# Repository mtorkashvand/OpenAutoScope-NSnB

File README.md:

# OpenAutoScope-NSnB
OpenAutoScope is a bright-field tracking microscope capable of delivering light stimulus to freely behaing c. elegans. This system is designed and assembled by Nate Cermak 
and the ripository containing information on how to assemble the system is found here:  
[OpenAutoScope by Nate Cermak](https://bitbucket.org/natecermak/openautoscope/src/master/)  
For convenience I have copied the content of the mentioned repository here.  

OpenAutoScope-NSnB repository is an open-source software developed during the NSnB 2022 program to pilot the system.

## Installation

1- Clone this repository:  
```
git clone https://github.com/mtorkashvand/OpenAutoScope-NSnB.git
```  
2- Navigate into the clone repo and use the `.yml` file to create a conda environment named `wormtracker`:  
```
cd OpenAutoScope-NSnB  
conda env create -f environment.yml  
```  
3- Activate `wormtracker` environment and install the software inside it:  
```  
activate wormtracker  
python setup.py develop  
```  
4- Open a File Explorer window and navigate to `OpenAutoScope-NSnB -> wormtracker_scope -> bin -> debug`, then click on the address bar and copy the absolute path to this folder.  

5- In the Windows search bar type `edit the system environment variables` and open it.  

6- Click on `Environment Variables ...`  

7- In the opened window, under `System Varibales` click on `New ...`  

8- Set the variable name to `WORMTRACKER_BIN` and set the variable value to the absolute path copied in step 4, and click on `OK`  

9- Next, look for the `Path` variable under the `System Variables`, double-click to open it, click on `New` and add `%WORMTRACKER_BIN%` and click on `OK`  

The Installation is completed  

## Running the System

1. Open a command prompt, and activate `wormtracker` environment  
```
activate wormtracker
```
2. Run the system using the following command:
```
wormtracker --directory=<data output path> --exposure=<exposure time in microseconds>
```  
exapmle: if you want your data to be saved in a folder named `data` in the C drive, and the exposure time is 1500us, then the command to run the system is:  
```
wormtracker --directory=C:\data --exposure=1500
```  
Note: A default value for the exposure time and the data directory could be set in `wormtracker.py` file which is located here:  
```
OpenAutoScope-NSnB -> wormtracker_scope -> system
```
If you want to run the system with those default values, you can run the system just by typing: (step 1 is still necessary)
```
wormtracker
``` 

## Operating the system

Once you run the system, a displayer window pops up and streams the camera feed. At this point, the command prompt window is just to print messages and we do not use it to send any commands. To make the operation easier, a Xbox controller is used to send different commands to the system. The below figure explains which buttons are programmed, and what each one does.  

### Example:  
- Once the system is running and you see the `FlirCamera: Initialized.` in the command prompt, press `X` on the Xbox controller to turn on the light source.  
- You can adjust the Z speed by the left-right shoulders, set the speed to 256 and move upward until you are focused in Z. For a better focus you might want to move slower once you are closer to the focus point.  
- Use the fine or coarse X-Y translation to locate the worm. A black rectangle shows the detected object by the tracking algorithm. If the animal is perfectly inscribed inside the rectangle, you can go ahead and press `A` to start tracking.  
- The tracking algorithm tracks the animals in X, Y and Z directions. You can start recording the data by pressing `B` on the Xbox controller.  
Note: The tracking and recording could be toggled using the Xbox controller, but at the same time the status is printed on the command prompt as well.  
- At any point, use the `Y` button to toggle the light stimulus during the experiment.  
Note: Each time you toggle the recorder, a new file is created.  
- Once you are done, you can type `DO shutdown` in the command prompt to shutdown the system.  

## Accessing the data

This software uses the HDF data format to save the recordings, but for convenience a video writer is added to the software to convert your recordings into MP4 movies. The MP4 movies are not generated for all recordings automatically in real time. To generate a MP4 movie for a recording:  
1- Activate the `wormtracker` environment  
```
activate wormtracker
```  
2- Locate the dataset of interest and copy its name and run the following command:  
```
wormtracker_video_writer --directory=<absolute data path> --file=<file name> --fps=<required frame rate for the movie>
```

For example if the data file is saved at `C:\data` and the file name is `flircamera_2022_12_07_14_05_25.h5` and the frame rate for the movie is decided to be 10Hz, then the following command generates the MP4 video for this specific dataset in the same directory:  
```
wormtracker_video_writer --directory=C:\data --file=flircamera_2022_12_07_14_05_25 --fps=10
```

## Optimizing the Tracking Algorithm

There are 2 parameters that could be adjusted for each experiment for a better tracking result.  
1. The cameras exposure time: In 'Running the system` one of the parameters is the exposure in microseconds. To decide the best value for this parameter, look at the displayer when you toggle the light source (The X button on the Xbox controller). If when you turn on the light source, you see that for a few frames right after that, the displayer is saturated (the displayer shows a all-white screen), it means that the exposure is too high and the displayer needs to adjust the output. Shutdown the system, and decrease the exposure until the situation with saturation is improved.  
2. The second parameter is the threshold value that is used to convert the greyscale image taken by the camera to a binary image. The threshold value could be adjusted using the left-right pads on the xbox controller. The tracker is robust to small changes in the value of the threshold close to the middle of the range (it can have values from 0 to 255). If the detected rectangle is far bigger than the animal, increase the threshold value. If the detected rectangle does not include some parts of the worm (the worm is not inscribed in it), try decreasing the value of the threshold parameter.  

Note: unlike the exposure time, to change the threshold value you do not need to shutdown the system.  

## Operation Notes:

- Before running the system, the motors could be rotated manually, but when the system is running, the motors are locked. The location of the motors at the time that the system is initiated are set as zeros. The Z motor does not go lower than this initial position for safety reasons, and the X-Y values change by around 2cm in each direction. So before you run the system, manually lower Z to a point that it is right above the objective but not touching, and try to move the x-y motors until the objective is centered relative to the worm plate. At the end of the experiment, when the `DO shutdown` command is send to shutdown the system, the motors move back to their 0 position. What it means is that as long as motors are not moved manually between experiments, you only need to set the initial position manually once.

- The teensy is connected to the computer with a micro USB cable, there is a parameter named `teensy_usb_port` in the `wormtracker.py` file ( `OpenAutoScope-NSnB -> wormtracker_scope -> system` ) which needs to be set to the port number for this USB cable. As long as it is not disconnected and connected to another port, this variable has to be set once  

## Author notes

The author of this README.md file is Mahdi Torkashvand (mmt.mahdi@gmail.com)
Please reach out with your questions/suggestions.

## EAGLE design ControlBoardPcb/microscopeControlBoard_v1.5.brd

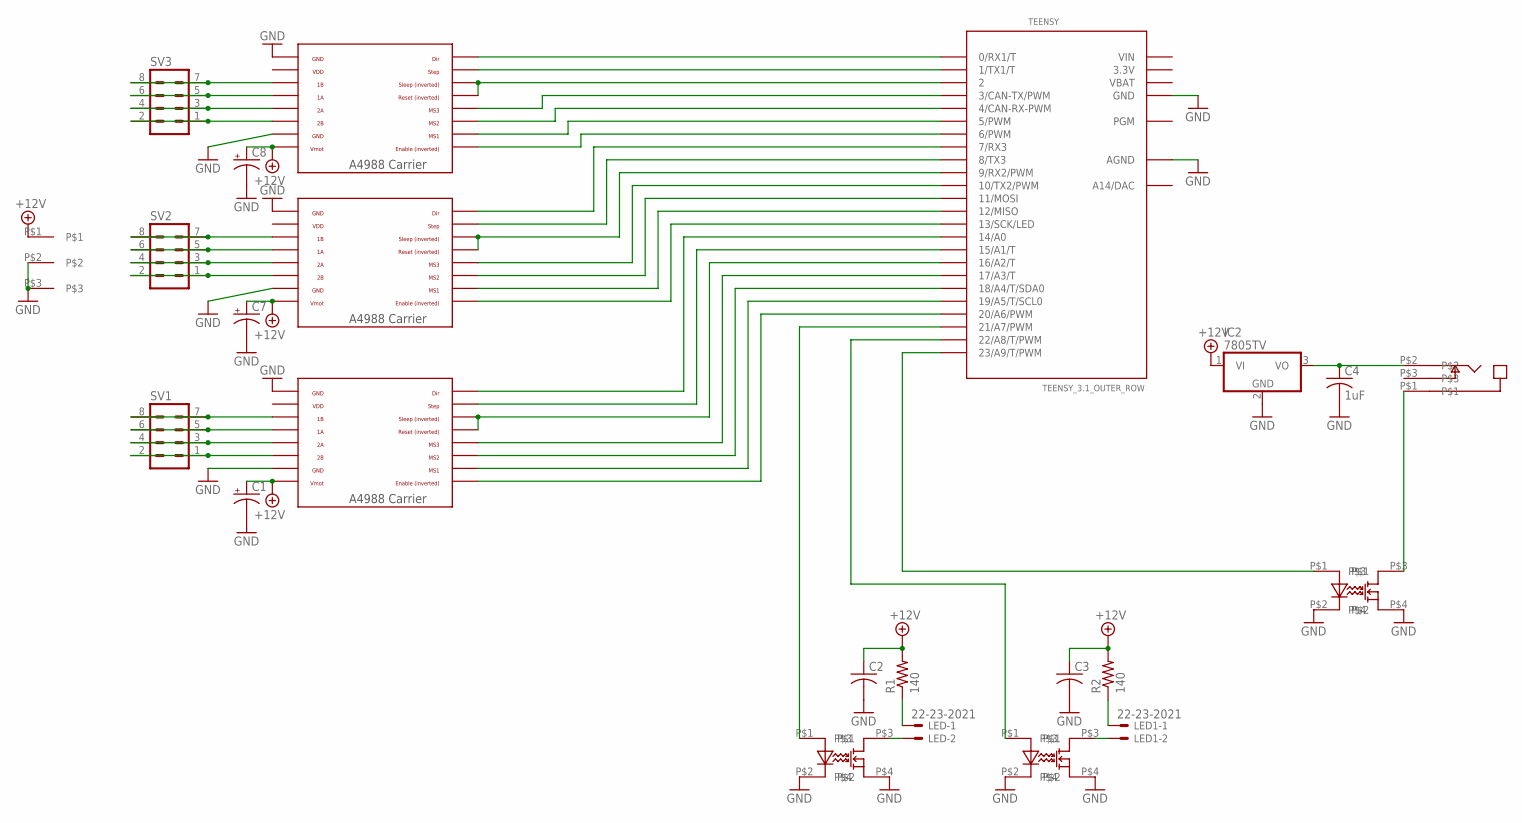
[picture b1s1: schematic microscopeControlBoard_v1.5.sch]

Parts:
C1, C7, C8: CAP_POLPTH4; CPOL-RADIAL-1000UF-25V
C2, C3: C-USC0805; C0805
C4: 1uF; C0805
DRV8825_1: A4983CARRIER; A4988BREAKOUT
IC2: 7805TV; TO220V
LED, LED1: 22-23-2021; MPN 22-23-2021
R1, R2: 140; R2512
SV1, SV2, SV3: MA04-2
TEENSY: TEENSY_3.1_OUTER_ROW; TEENSY3-OUTER_ROW
U$1, U$3: A4983CARRIER; A4988BREAKOUT
U$2, U$5, U$6: CPC1002
U$4: PWRJACK2
U$7: CP-2523MJCT-ND

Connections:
3.3V: TEENSY.3.3V, TEENSY.3.3V1 (3.3V)
+12V: C1.+, C2.1, C3.1, C7.+, C8.+, DRV8825_1.VMOT, IC2.1 (VI), R1.2, R2.2, U$1.VMOT, U$3.VMOT, U$4.P$1
GND: C1.-, C2.2, C3.2, C4.2, C7.-, C8.-, DRV8825_1.GND, DRV8825_1.GND@0 (GND), IC2.2 (GND), TEENSY.AGND, TEENSY.GND, TEENSY.GND1 (GND), U$1.GND, U$1.GND@0 (GND), U$2.P$2, U$2.P$4, U$3.GND, U$3.GND@0 (GND), U$4.P$2, U$4.P$3, U$5.P$2, U$5.P$4, U$6.P$2, U$6.P$4
unnamed: LED.1, R1.1
unnamed: TEENSY.22/A8 (22/A8/T/PWM), U$2.P$1
unnamed: DRV8825_1.DIR, TEENSY.0 (0/RX1/T)
unnamed: DRV8825_1.STEP, TEENSY.1 (1/TX1/T)
unnamed: DRV8825_1.RST, DRV8825_1.SLP (SLEEP), TEENSY.2
unnamed: TEENSY.9 (9/RX2/PWM), U$3.RST, U$3.SLP (SLEEP)
unnamed: TEENSY.7 (7/RX3), U$3.DIR
unnamed: TEENSY.8 (8/TX3), U$3.STEP
unnamed: TEENSY.14/A0, U$1.DIR
unnamed: TEENSY.15/A1 (15/A1/T), U$1.STEP
unnamed: TEENSY.16/A2 (16/A2/T), U$1.RST, U$1.SLP (SLEEP)
unnamed: DRV8825_1.EN, TEENSY.6 (6/PWM)
unnamed: LED1.2, U$2.P$3
unnamed: TEENSY.17/A3 (17/A3/T), U$1.MS3
unnamed: TEENSY.18/A4 (18/A4/T/SDA0), U$1.MS2
unnamed: TEENSY.19/A5 (19/A5/T/SCL0), U$1.MS1
unnamed: TEENSY.20/A6 (20/A6/PWM), U$1.EN
unnamed: DRV8825_1.1B, SV3.7, SV3.8
unnamed: DRV8825_1.1A, SV3.5, SV3.6
unnamed: DRV8825_1.2A, SV3.3, SV3.4
unnamed: DRV8825_1.2B, SV3.1, SV3.2
unnamed: SV2.7, SV2.8, U$3.1B
unnamed: SV2.5, SV2.6, U$3.1A
unnamed: SV2.3, SV2.4, U$3.2A
unnamed: SV2.1, SV2.2, U$3.2B
unnamed: SV1.7, SV1.8, U$1.1B
unnamed: LED1.1, R2.1
unnamed: TEENSY.21/A7 (21/A7/PWM), U$6.P$1
unnamed: SV1.5, SV1.6, U$1.1A
unnamed: LED.2, U$6.P$3
unnamed: TEENSY.23/A9 (23/A9/T/PWM), U$5.P$1
unnamed: SV1.3, SV1.4, U$1.2A
unnamed: TEENSY.13 (13/SCK/LED), U$3.EN
unnamed: DRV8825_1.MS3, TEENSY.3 (3/CAN-TX/PWM)
unnamed: DRV8825_1.MS2, TEENSY.4 (4/CAN-RX-PWM)
unnamed: DRV8825_1.MS1, TEENSY.5 (5/PWM)
unnamed: SV1.1, SV1.2, U$1.2B
unnamed: TEENSY.10 (10/TX2/PWM), U$3.MS3
unnamed: TEENSY.11 (11/MOSI), U$3.MS2
unnamed: TEENSY.12 (12/MISO), U$3.MS1
unnamed: C4.1, IC2.3 (VO), U$7.P$2
unnamed: U$5.P$3, U$7.P$1
VBAT: TEENSY.VBAT
VDD: DRV8825_1.VDD, U$1.VDD, U$3.VDD
VIN: TEENSY.VIN

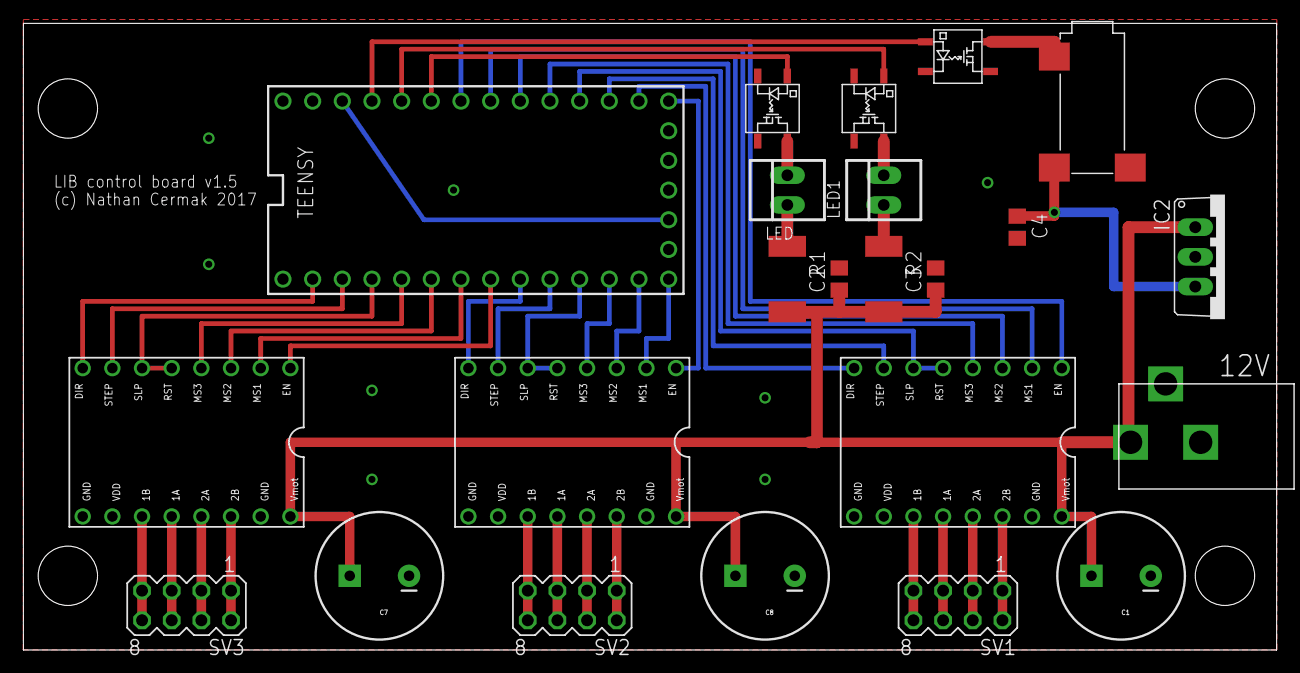
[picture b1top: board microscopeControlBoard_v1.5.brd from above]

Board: 2 copper layers, 107.3 x 53.6 mm, 23 parts (0 on the bottom side), 46 nets.

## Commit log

2022-12-07 Add all files and folders
2022-12-07 Add a new command line argument: directory

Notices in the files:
parts and their libraries:
SparkFun-Capacitors: Licensing: Creative Commons ShareAlike 4.0 International - https://creativecommons.org/licenses/by-sa/4.0
